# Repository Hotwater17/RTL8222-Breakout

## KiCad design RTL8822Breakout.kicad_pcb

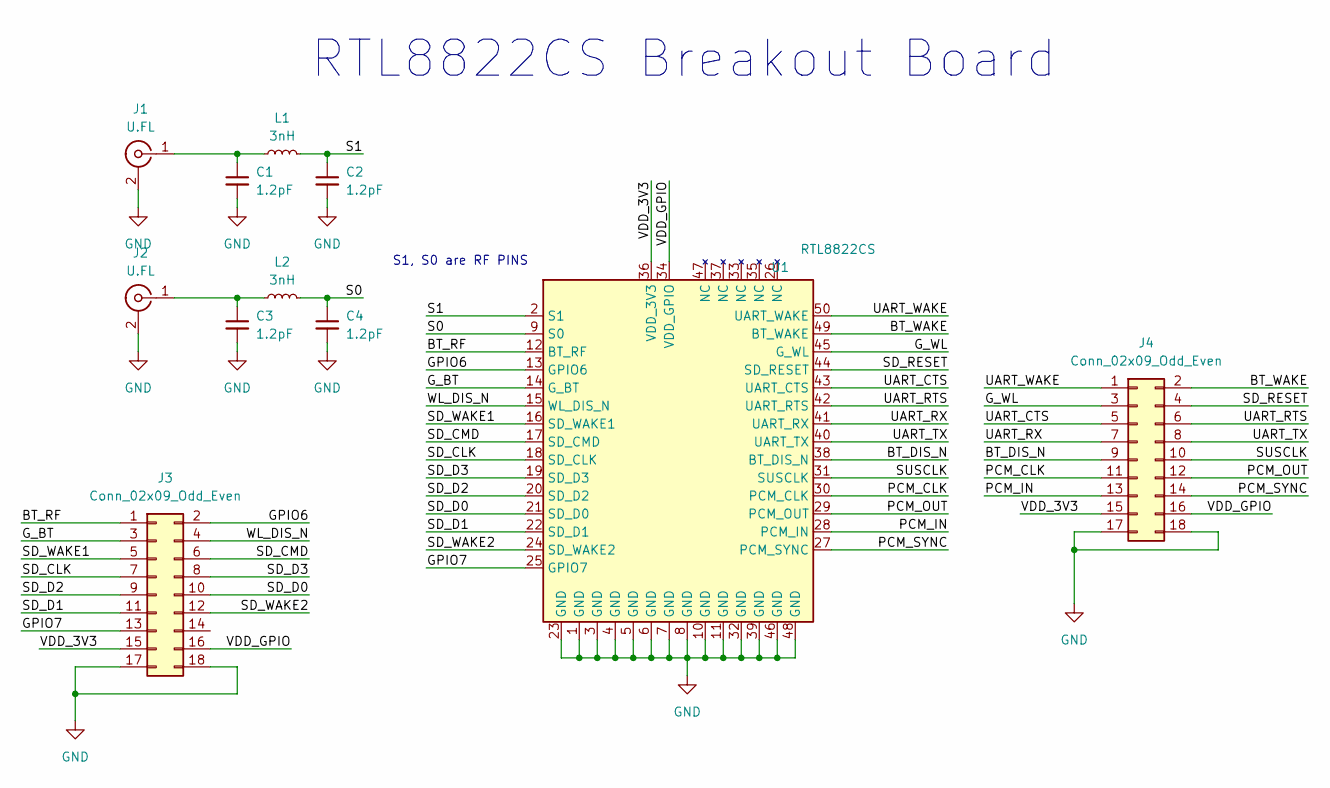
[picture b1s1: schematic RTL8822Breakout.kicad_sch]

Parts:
C1, C2, C3, C4: 1.2pF; C_0805_2012Metric
J1, J2: U.FL; IPEX-SMD_BWIPX-1-001E; LCSC C5137195
J3, J4: Conn_02x09_Odd_Even; PinHeader_2x09_P2.54mm_Vertical
L1, L2: 3nH; L_0805_2012Metric
U1: RTL8822CS

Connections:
/BT_DIS_N: J4.9, U1.38 (BT_DIS_N)
/BT_RF: J3.1, U1.12 (BT_RF)
/BT_WAKE: J4.2, U1.49 (BT_WAKE)
/GPIO6: J3.2, U1.13 (GPIO6)
/GPIO7: J3.13, U1.25 (GPIO7)
/G_BT: J3.3, U1.14 (G_BT)
/G_WL: J4.3, U1.45 (G_WL)
/PCM_CLK: J4.11, U1.30 (PCM_CLK)
/PCM_IN: J4.13, U1.28 (PCM_IN)
/PCM_OUT: J4.12, U1.29 (PCM_OUT)
/PCM_SYNC: J4.14, U1.27 (PCM_SYNC)
/S0: C4.1, L2.2, U1.9 (S0)
/S1: C2.1, L1.2, U1.2 (S1)
/SD_CLK: J3.7, U1.18 (SD_CLK)
/SD_CMD: J3.6, U1.17 (SD_CMD)
/SD_D0: J3.10, U1.21 (SD_D0)
/SD_D1: J3.11, U1.22 (SD_D1)
/SD_D2: J3.9, U1.20 (SD_D2)
/SD_D3: J3.8, U1.19 (SD_D3)
/SD_RESET: J4.4, U1.44 (SD_RESET)
/SD_WAKE1: J3.5, U1.16 (SD_WAKE1)
/SD_WAKE2: J3.12, U1.24 (SD_WAKE2)
/SUSCLK: J4.10, U1.31 (SUSCLK)
/UART_CTS: J4.5, U1.43 (UART_CTS)
/UART_RTS: J4.6, U1.42 (UART_RTS)
/UART_RX: J4.7, U1.41 (UART_RX)
/UART_TX: J4.8, U1.40 (UART_TX)
/UART_WAKE: J4.1, U1.50 (UART_WAKE)
/VDD_3V3: J3.15, J4.15, U1.36 (VDD_3V3)
/VDD_GPIO: J3.16, J4.16, U1.34 (VDD_GPIO)
/WL_DIS_N: J3.4, U1.15 (WL_DIS_N)
GND: C1.2, C2.2, C3.2, C4.2, J1.2 (Ext), J1.3, J2.2 (Ext), J2.3, J3.17, J3.18, J4.17, J4.18, U1.1 (GND), U1.3 (GND), U1.4 (GND), U1.5 (GND), U1.6 (GND), U1.7 (GND), U1.8 (GND), U1.10 (GND), U1.11 (GND), U1.23 (GND), U1.32 (GND), U1.39 (GND), U1.46 (GND), U1.48 (GND)
unnamed: C1.1, J1.1 (In), L1.1
unnamed: C3.1, J2.1 (In), L2.1

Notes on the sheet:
RTL8822CS Breakout Board
S1, S0 are RF PINS

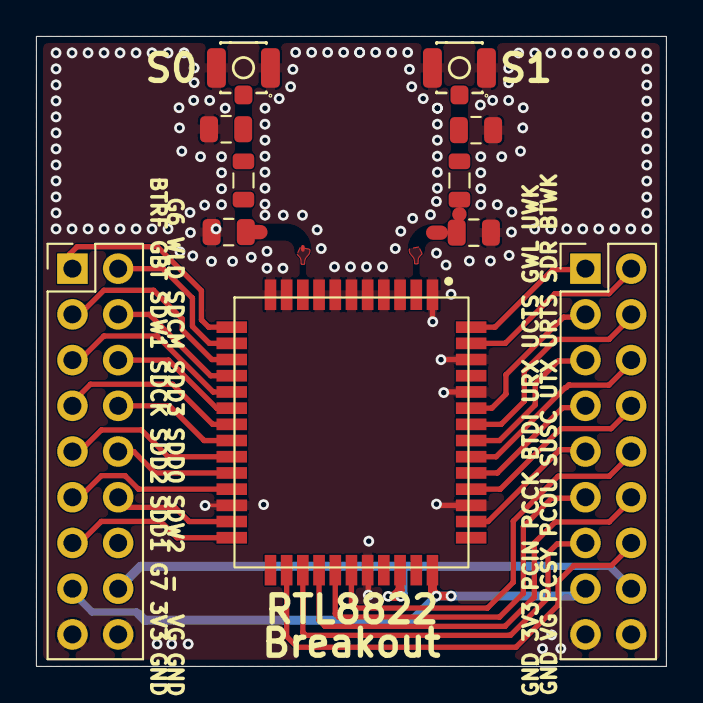
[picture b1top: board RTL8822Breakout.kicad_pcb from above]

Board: 2 copper layers, 35.0 x 35.0 mm, 11 parts (0 on the bottom side), 34 nets.

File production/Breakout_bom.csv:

Designator,Footprint,Quantity,Value,LCSC Part #
"C1, C2, C3, C4",0805,4,1.2pF,
"J1, J2",IPEX-SMD_BWIPX-1-001E,2,U.FL,C5137195
"J3, J4",PinHeader_2x09_P2.54mm_Vertical,2,Conn_02x09_Odd_Even,
"L1, L2",0805,2,3nH,
U1,RTL8822CS,1,RTL8822CS,

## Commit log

2026-05-11 Rev 0.1 Design, 2-layer board with coplanar waveguide RF tracks (0.8mm width, 0.2mm separation)
2026-05-11 Added teardrops and removed the soldermask from RF tracks
2026-05-11 Regenerated production files Rev. 0.1
